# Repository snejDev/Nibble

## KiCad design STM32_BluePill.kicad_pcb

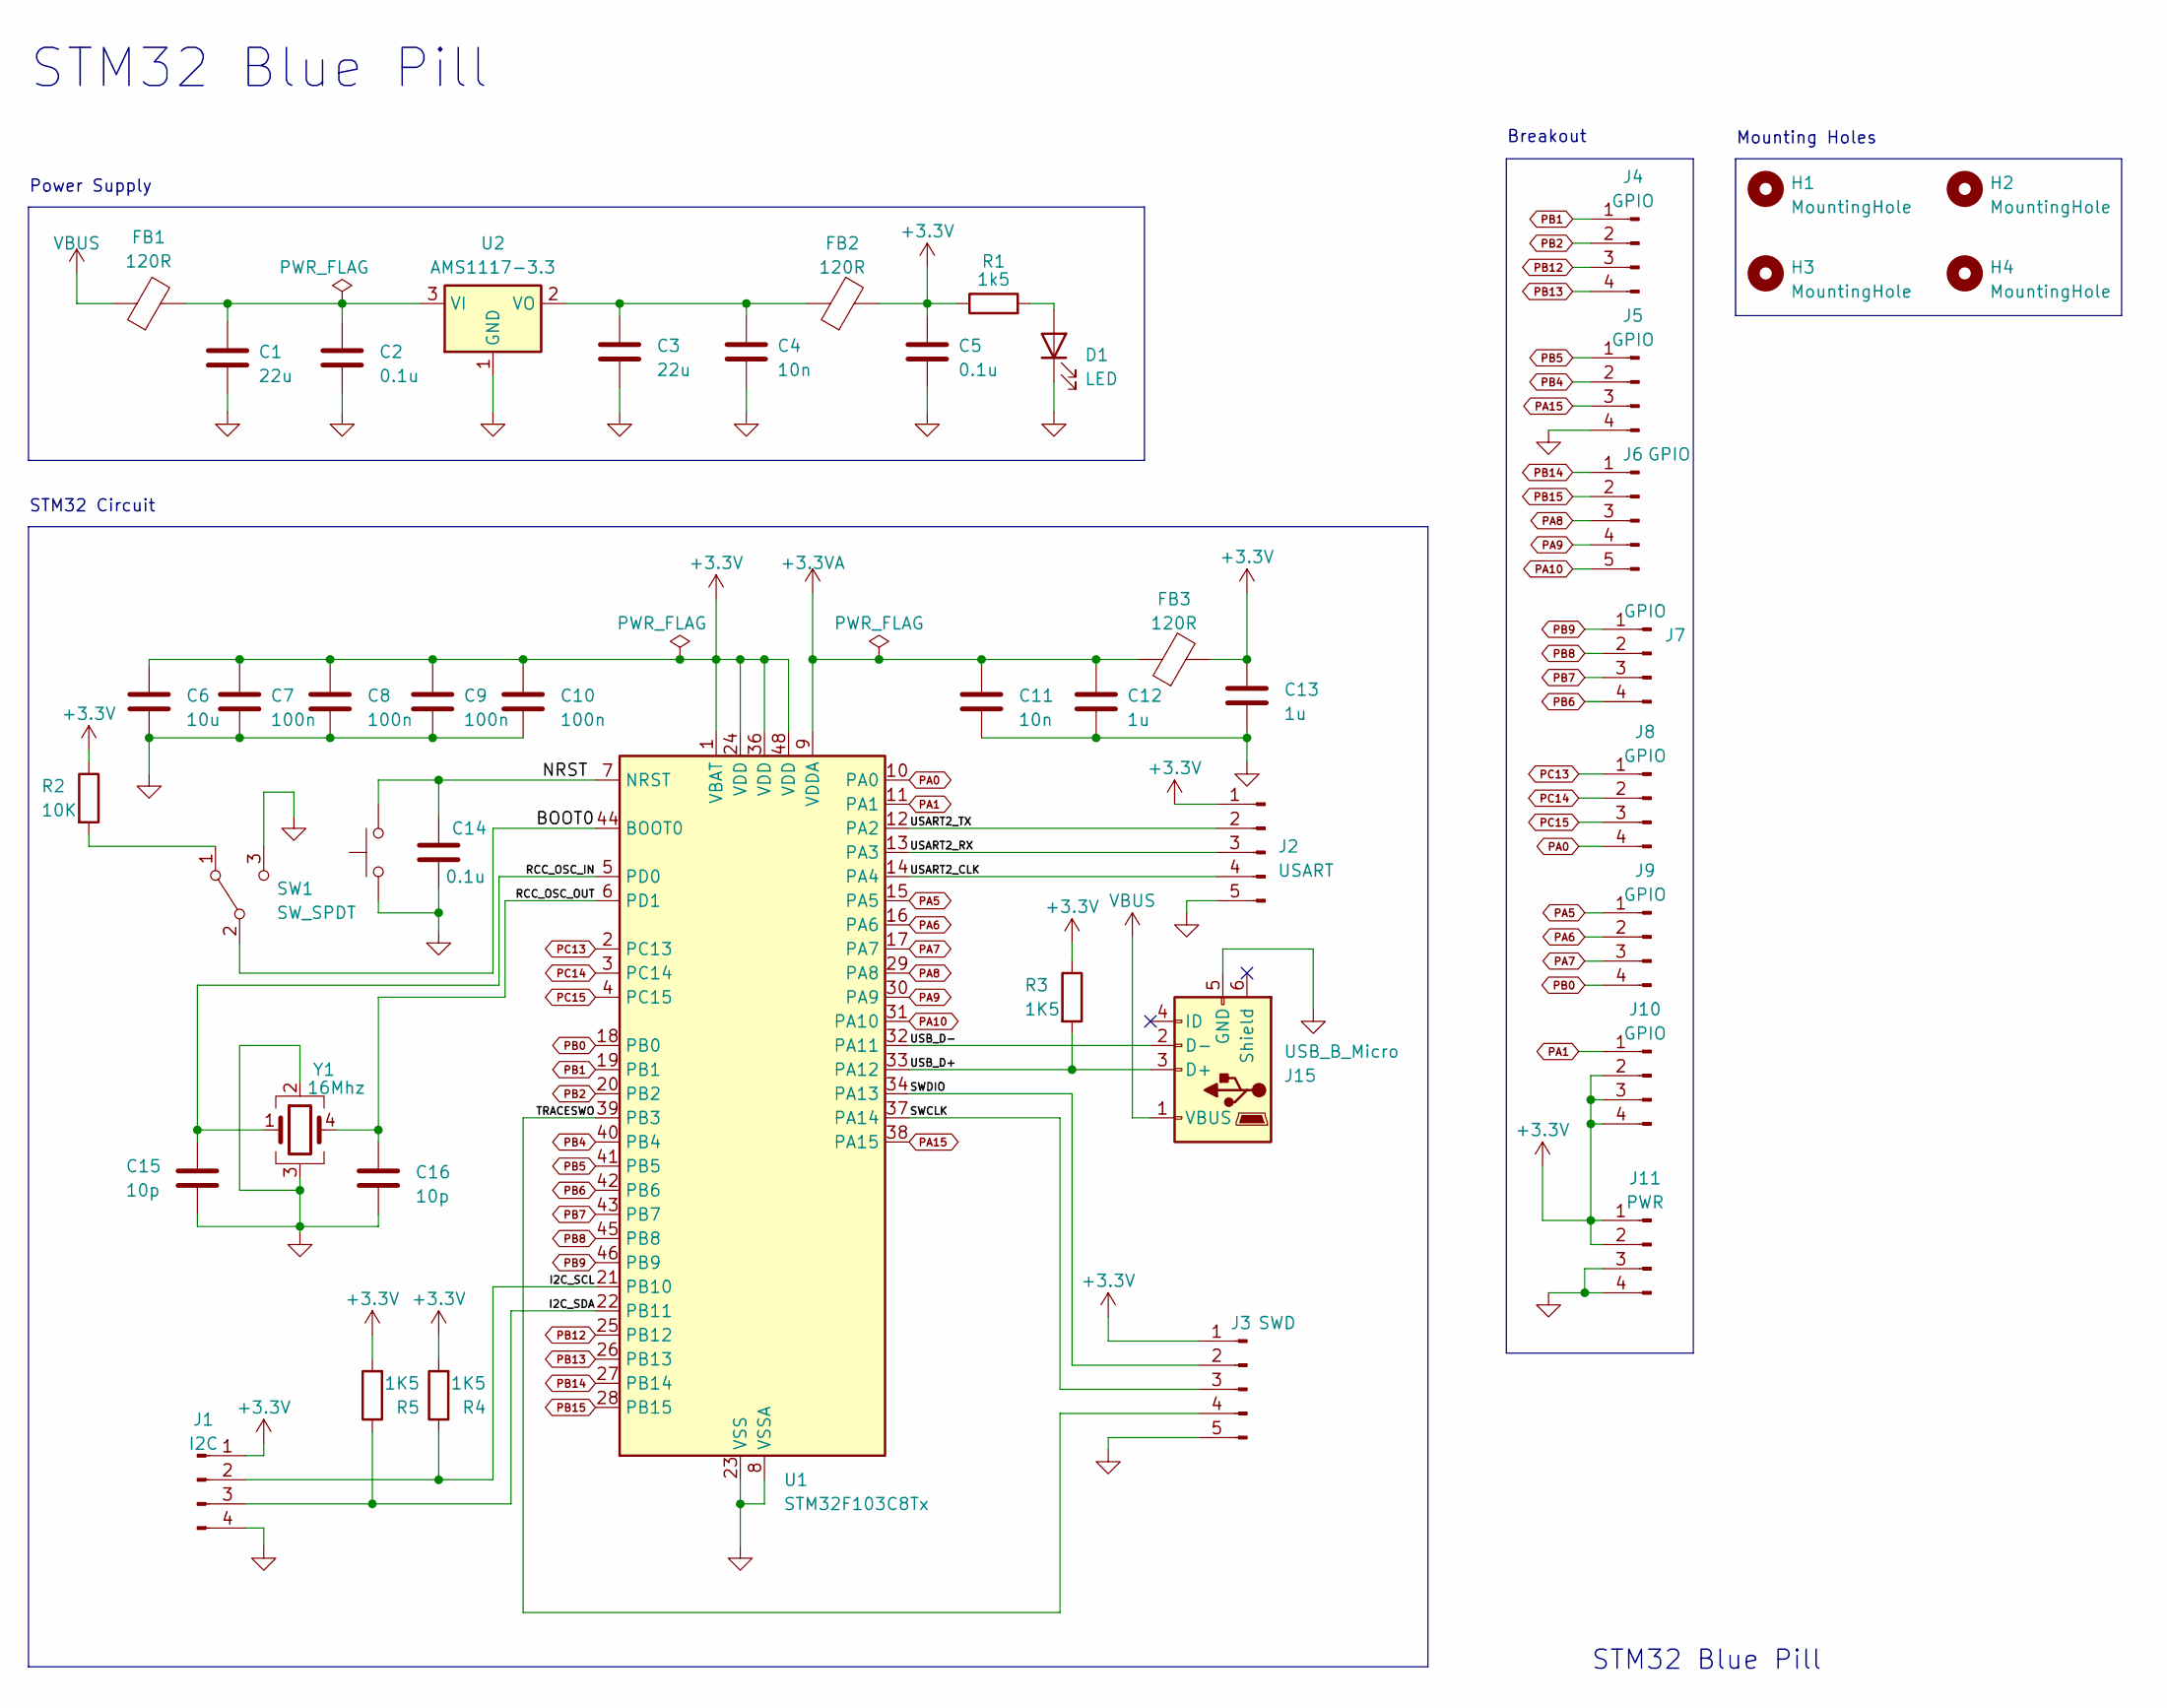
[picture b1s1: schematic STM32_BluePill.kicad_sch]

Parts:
C1, C3: 22u; C_0805_2012Metric
C2, C5, C14: 0.1u; C_0402_1005Metric
C4, C11: 10n; C_0402_1005Metric
C6: 10u; C_0603_1608Metric
C7, C8, C9, C10: 100n; C_0402_1005Metric
C12, C13: 1u; C_0402_1005Metric
C15, C16: 10p; C_0402_1005Metric
D1: LED; LED_0603_1608Metric
FB1, FB2, FB3: 120R; L_0603_1608Metric
H1, H2, H3, H4: MountingHole; MountingHole_2.2mm_M2
J1: I2C; PinHeader_1x04_P2.54mm_Vertical
J2: USART; PinHeader_1x05_P2.54mm_Vertical
J3: SWD; PinHeader_1x05_P2.54mm_Vertical
J4, J5, J7, J8, J9, J10: GPIO; PinHeader_1x04_P2.54mm_Vertical
J6: GPIO; PinHeader_1x05_P2.54mm_Vertical
J11: PWR; PinHeader_1x04_P2.54mm_Vertical
J15: USB_B_Micro; USB_Micro-B_Wuerth_629105150521_CircularHoles
R1: 1k5; R_0402_1005Metric
R2: 10K; R_0402_1005Metric
R3, R4, R5: 1K5; R_0402_1005Metric
SW1: SW_SPDT; SW_SPDT_PCM12
SW2: SW_Push; SW_PUSH_6mm
U1: STM32F103C8Tx; LQFP-48_7x7mm_P0.5mm
U2: AMS1117-3.3; SOT-223-3_TabPin2
Y1: 16Mhz; Crystal_SMD_3225-4Pin_3.2x2.5mm_HandSoldering

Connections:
+3.3V: C5.1, C6.1, C7.1, C8.1, C9.1, C10.1, C13.1, FB2.2, FB3.2, J1.1, J2.1, J3.1, J10.2, J10.3, J10.4, J11.1, J11.2, R1.1, R2.1, R3.1, R4.2, R5.2, U1.1 (VBAT), U1.24 (VDD), U1.36 (VDD), U1.48 (VDD)
+3.3VA: C11.1, C12.1, FB3.1, U1.9 (VDDA)
/BOOT0: SW1.2 (B), U1.44 (BOOT0)
/I2C_SCL: J1.2, R4.1, U1.21 (PB10)
/I2C_SDA: J1.3, R5.1, U1.22 (PB11)
/NRST: C14.1, SW2.2, U1.7 (NRST)
/RCC_OSC_IN: C15.1, U1.5 (PD0), Y1.1
/RCC_OSC_OUT: C16.1, U1.6 (PD1), Y1.4
/SWCLK: J3.3, U1.37 (PA14)
/SWDIO: J3.2, U1.34 (PA13)
/TRACESWO: J3.4, U1.39 (PB3)
/USART2_CLK: J2.4, U1.14 (PA4)
/USART2_RX: J2.3, U1.13 (PA3)
/USART2_TX: J2.2, U1.12 (PA2)
/USB_D+: J15.3 (D+), R3.2, U1.33 (PA12)
/USB_D-: J15.2 (D-), U1.32 (PA11)
GND: C1.2, C2.2, C3.2, C4.2, C5.2, C6.2, C7.2, C8.2, C9.2, C10.2, C11.2, C12.2, C13.2, C14.2, C15.2, C16.2, D1.1 (K), J1.4, J2.5, J3.5, J5.4, J11.3, J11.4, J15.5 (GND), SW1.3 (C), SW2.1, U1.8 (VSSA), U1.23 (VSS), U1.35 (VSS), U1.47 (VSS), U2.1 (GND), Y1.2, Y1.3
unnamed: D1.2 (A), R1.2
unnamed: R2.2, SW1.1 (A)
unnamed: C1.1, C2.1, FB1.2, U2.3 (VI)
unnamed: C3.1, C4.1, FB2.1, U2.2 (VO)
PA0: J8.4, U1.10 (PA0)
PA1: J10.1, U1.11 (PA1)
PA5: J9.1, U1.15 (PA5)
PA6: J9.2, U1.16 (PA6)
PA7: J9.3, U1.17 (PA7)
PA8: J6.3, U1.29 (PA8)
PA9: J6.4, U1.30 (PA9)
PA10: J6.5, U1.31 (PA10)
PA15: J5.3, U1.38 (PA15)
PB0: J9.4, U1.18 (PB0)
PB1: J4.1, U1.19 (PB1)
PB2: J4.2, U1.20 (PB2)
PB4: J5.2, U1.40 (PB4)
PB5: J5.1, U1.41 (PB5)
PB6: J7.4, U1.42 (PB6)
PB7: J7.3, U1.43 (PB7)
PB8: J7.2, U1.45 (PB8)
PB9: J7.1, U1.46 (PB9)
PB12: J4.3, U1.25 (PB12)
PB13: J4.4, U1.26 (PB13)
PB14: J6.1, U1.27 (PB14)
PB15: J6.2, U1.28 (PB15)
PC13: J8.1, U1.2 (PC13)
PC14: J8.2, U1.3 (PC14)
PC15: J8.3, U1.4 (PC15)
VBUS: FB1.1, J15.1 (VBUS)

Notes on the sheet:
Breakout
STM32 Blue Pill
Mounting Holes
STM32 Circuit
Power Supply

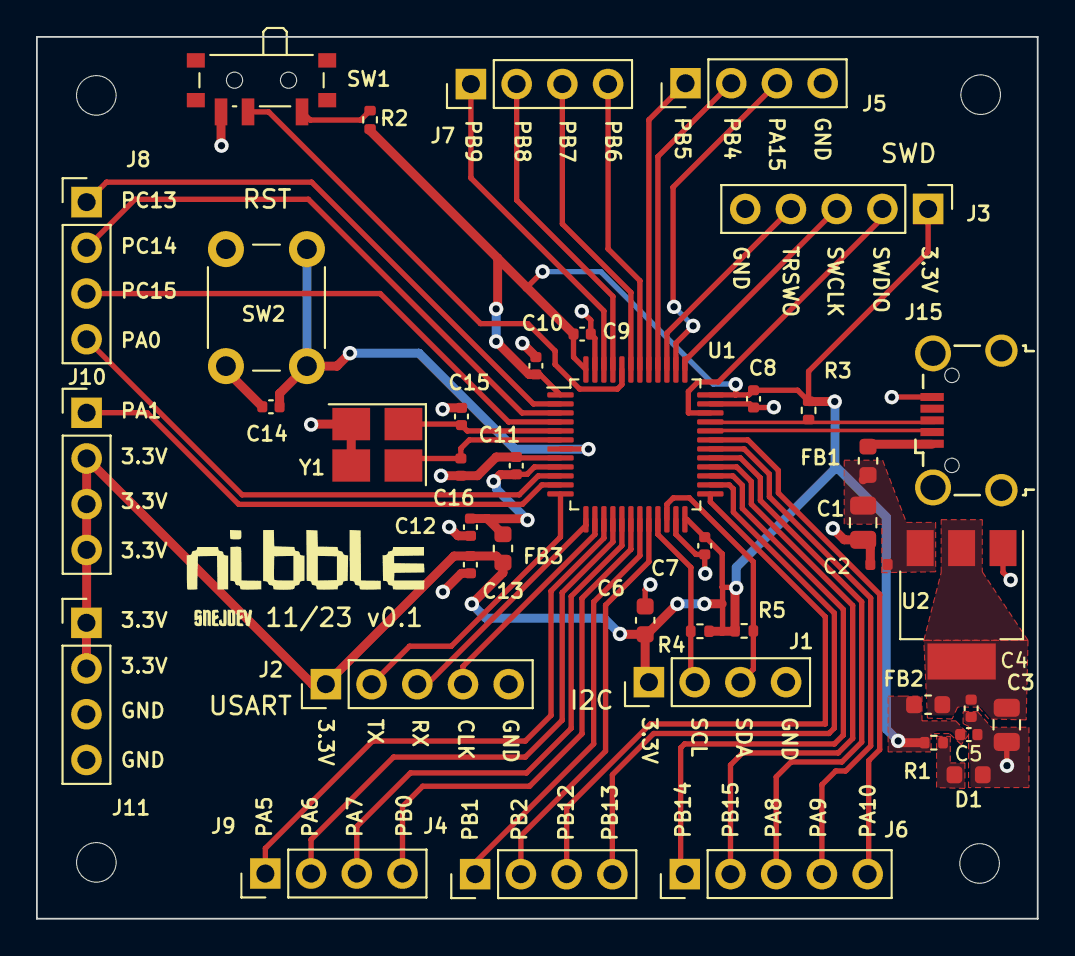
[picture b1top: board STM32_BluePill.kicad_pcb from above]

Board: 2 copper layers, 55.6 x 49.0 mm, 46 parts (0 on the bottom side), 47 nets.
